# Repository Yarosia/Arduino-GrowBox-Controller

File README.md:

# Arduino GrowBox Controller

Additional documentation can be found at [Red Sheep Labs](https://www.yarosia.it/).

## Recent Changes
- 0.7.7 - 09 Jan 2019
  - First Commit

## Current Status: Testing

My GrowBox is running this firmware from January 2017. Peppers born and grow healty until placed outdoor. 
__I do not assume any responsability for any damage to persons, plants or thing by using this software.__

## License

Arduino GrowBox Controller is published under the [GPL license](/LICENSE) because we believe in open development. The GPL comes with both rights and obligations. Whether you use this GrowBox firmware as the driver for your open or closed-source product, you must keep it open, and you must provide your compatible source code to end users upon request. The most straightforward way to comply with the license is to make a fork of this project on Github, perform your modifications, and direct users to your modified fork.

While we can't prevent the use of this code in products (GrowBox, GermBox, Indoor Gardening etc.) that are closed source or crippled by a patent, we would prefer that you choose another firmware or, better yet, make your own.

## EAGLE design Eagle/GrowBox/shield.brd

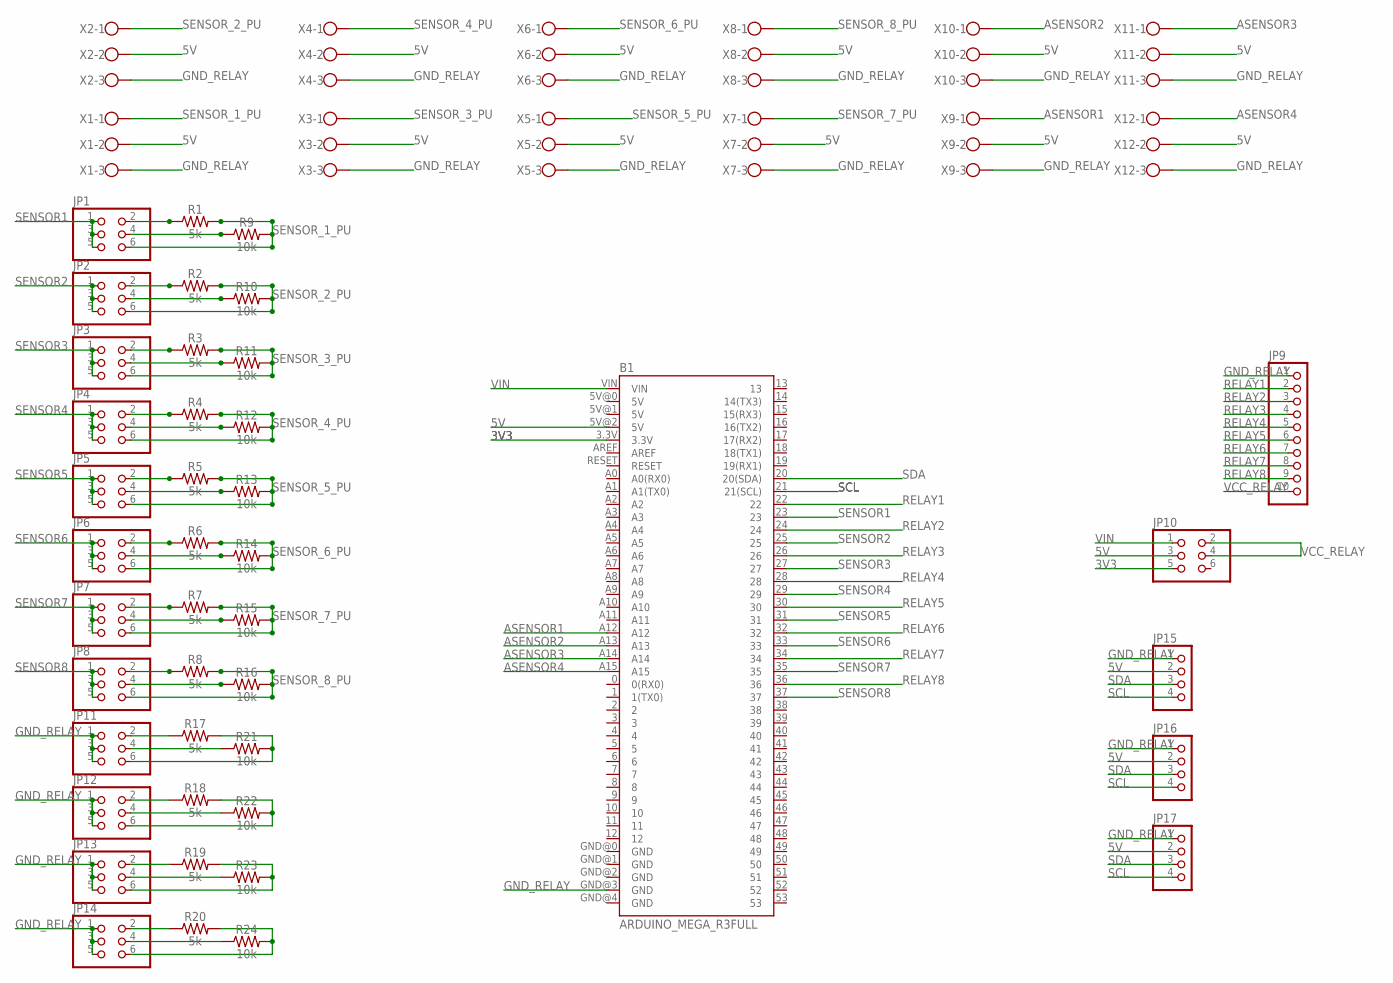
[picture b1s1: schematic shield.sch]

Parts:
B1: ARDUINO_MEGA_R3FULL; ARDUINO_MEGA
JP1, JP2, JP3, JP4, JP5, JP6, JP7, JP8, JP10, JP11, JP12, JP13, JP14: PINHD-2X3; 2X03
JP9: PINHD-1X10; 1X10
JP15, JP16, JP17: PINHD-1X4; 1X04
R1, R2, R3, R4, R5, R6, R7, R8, R17, R18, R19, R20: 5k; AXIAL-0.3
R9, R10, R11, R12, R13, R14, R15, R16, R21, R22, R23, R24: 10k; AXIAL-0.3
X1, X2, X3, X4, X5, X6, X7, X8, X9, X10, X11, X12: W237-103

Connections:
3V3: B1.3.3V, JP10.5
5V: B1.5V@2 (5V), JP10.3, JP15.2, JP16.2, JP17.2, X1.2, X2.2, X3.2, X4.2, X5.2, X6.2, X7.2, X8.2, X9.2, X10.2, X11.2, X12.2
ASENSOR1: B1.A12, X9.1
ASENSOR2: B1.A13, X10.1
ASENSOR3: B1.A14, X11.1
ASENSOR4: B1.A15, X12.1
GND_RELAY: B1.GND@3 (GND), JP9.1, JP11.1, JP11.3, JP11.5, JP12.1, JP12.3, JP12.5, JP13.1, JP13.3, JP13.5, JP14.1, JP14.3, JP14.5, JP15.1, JP16.1, JP17.1, X1.3, X2.3, X3.3, X4.3, X5.3, X6.3, X7.3, X8.3, X9.3, X10.3, X11.3, X12.3
unnamed: JP2.4, R10.P$1 (1)
unnamed: JP1.4, R9.P$1 (1)
unnamed: JP3.4, R11.P$1 (1)
unnamed: JP4.4, R12.P$1 (1)
unnamed: JP14.2, R20.P$1 (1)
unnamed: JP5.4, R13.P$1 (1)
unnamed: JP14.6, R20.P$2 (2), R24.P$2 (2)
unnamed: JP6.4, R14.P$1 (1)
unnamed: JP14.4, R24.P$1 (1)
unnamed: JP7.4, R15.P$1 (1)
unnamed: JP13.2, R19.P$1 (1)
unnamed: JP8.4, R16.P$1 (1)
unnamed: JP13.6, R19.P$2 (2), R23.P$2 (2)
unnamed: JP13.4, R23.P$1 (1)
unnamed: JP12.2, R18.P$1 (1)
unnamed: JP1.2, R1.P$1 (1)
unnamed: JP2.2, R2.P$1 (1)
unnamed: JP3.2, R3.P$1 (1)
unnamed: JP4.2, R4.P$1 (1)
unnamed: JP5.2, R5.P$1 (1)
unnamed: JP6.2, R6.P$1 (1)
unnamed: JP7.2, R7.P$1 (1)
unnamed: JP8.2, R8.P$1 (1)
unnamed: JP12.6, R18.P$2 (2), R22.P$2 (2)
unnamed: JP12.4, R22.P$1 (1)
unnamed: JP11.2, R17.P$1 (1)
unnamed: JP11.6, R17.P$2 (2), R21.P$2 (2)
unnamed: JP11.4, R21.P$1 (1)
RELAY1: B1.22, JP9.2
RELAY2: B1.24, JP9.3
RELAY3: B1.26, JP9.4
RELAY4: B1.28, JP9.5
RELAY5: B1.30, JP9.6
RELAY6: B1.32, JP9.7
RELAY7: B1.34, JP9.8
RELAY8: B1.36, JP9.9
SCL: B1.21 (21(SCL)), JP15.4, JP16.4, JP17.4
SDA: B1.20 (20(SDA)), JP15.3, JP16.3, JP17.3
SENSOR1: B1.23, JP1.1, JP1.3, JP1.5
SENSOR2: B1.25, JP2.1, JP2.3, JP2.5
SENSOR3: B1.27, JP3.1, JP3.3, JP3.5
SENSOR4: B1.29, JP4.1, JP4.3, JP4.5
SENSOR5: B1.31, JP5.1, JP5.3, JP5.5
SENSOR6: B1.33, JP6.1, JP6.3, JP6.5
SENSOR7: B1.35, JP7.1, JP7.3, JP7.5
SENSOR8: B1.37, JP8.1, JP8.3, JP8.5
SENSOR_1_PU: JP1.6, R1.P$2 (2), R9.P$2 (2), X1.1
SENSOR_2_PU: JP2.6, R2.P$2 (2), R10.P$2 (2), X2.1
SENSOR_3_PU: JP3.6, R3.P$2 (2), R11.P$2 (2), X3.1
SENSOR_4_PU: JP4.6, R4.P$2 (2), R12.P$2 (2), X4.1
SENSOR_5_PU: JP5.6, R5.P$2 (2), R13.P$2 (2), X5.1
SENSOR_6_PU: JP6.6, R6.P$2 (2), R14.P$2 (2), X6.1
SENSOR_7_PU: JP7.6, R7.P$2 (2), R15.P$2 (2), X7.1
SENSOR_8_PU: JP8.6, R8.P$2 (2), R16.P$2 (2), X8.1
VCC_RELAY: JP9.10, JP10.2, JP10.4
VIN: B1.VIN, JP10.1

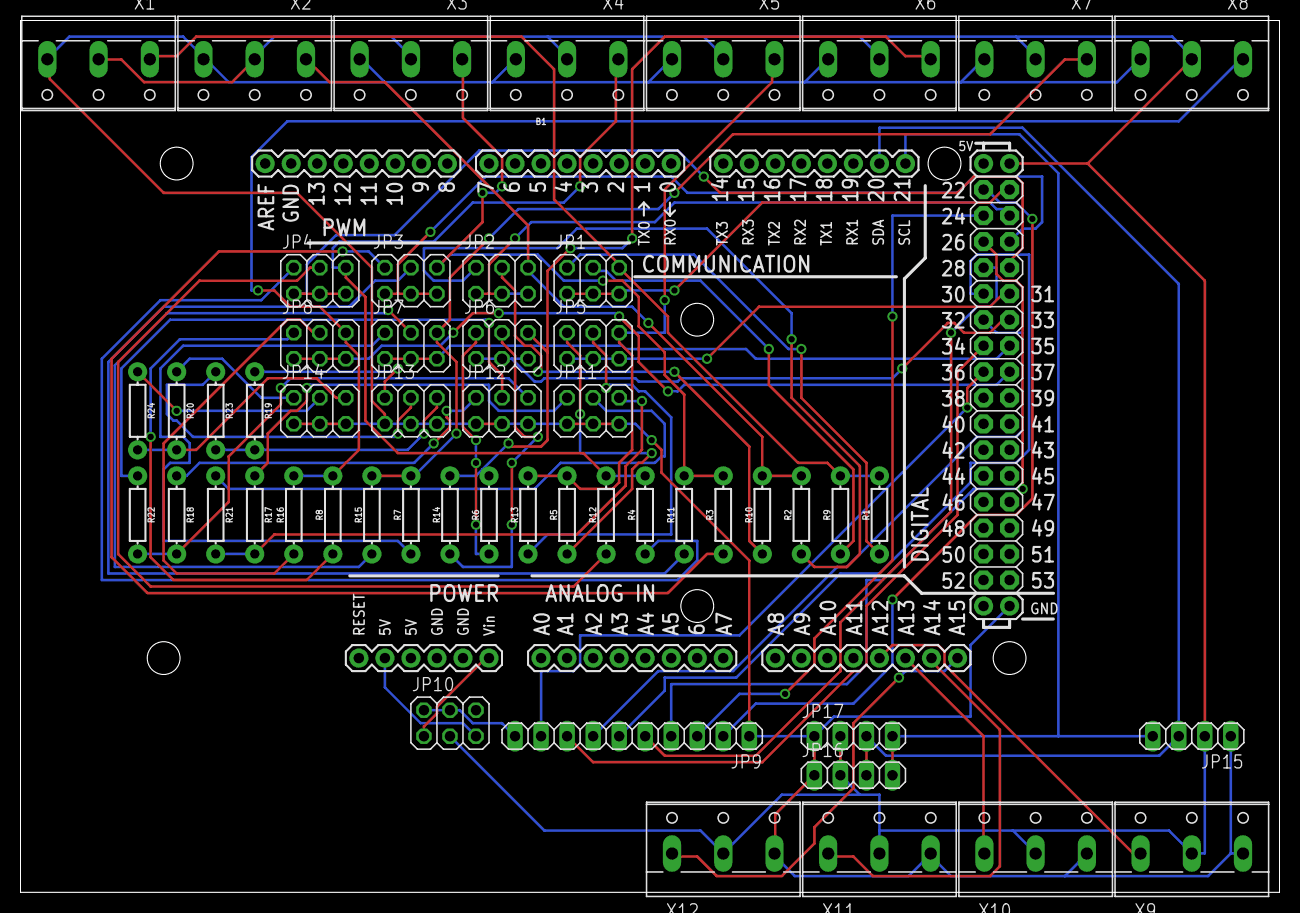
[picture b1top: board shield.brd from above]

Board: 2 copper layers, 122.9 x 85.1 mm, 54 parts (0 on the bottom side), 63 nets.

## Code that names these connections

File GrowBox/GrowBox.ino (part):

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}

void setRelays() {
  // RELAY1 (pin 6)
  if (StrContains(HTTP_req, "RELAY1=1")) {

    startLight();
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
    stopLight();
  }
  // RELAY2 (pin 7)
  if (StrContains(HTTP_req, "RELAY2=1")) {

    startHeater();
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
    stopHeater();
  }
  // RELAY3 (pin 8)
  if (StrContains(HTTP_req, "RELAY3=1")) {

    startFan();
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
    stopFan();
  }
  // RELAY4 (pin 9)
  if (StrContains(HTTP_req, "RELAY4=1")) {

    startWater();
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
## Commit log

2019-01-09 First Release
    Hello! This is the first release of the Arduino GrowBox Controller by Red Sheep Labs!
2019-01-09 Minor Corrections

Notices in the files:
GrowBox/GrowBox.ino:
Copyright (C): 2015-2018 Michele Valentini (www.yarosia.it - Red Sheep Labs)
This program is free software: you can redistribute it and/or modify
it under the terms of the GNU General Public License as published by
the Free Software Foundation, either version 3 of the License, or
(at your option) any later version.
parts and their libraries:
SparkFun-Boards: Licensing: Creative Commons ShareAlike 4.0 International - https://creativecommons.org/licenses/by-sa/4.0
